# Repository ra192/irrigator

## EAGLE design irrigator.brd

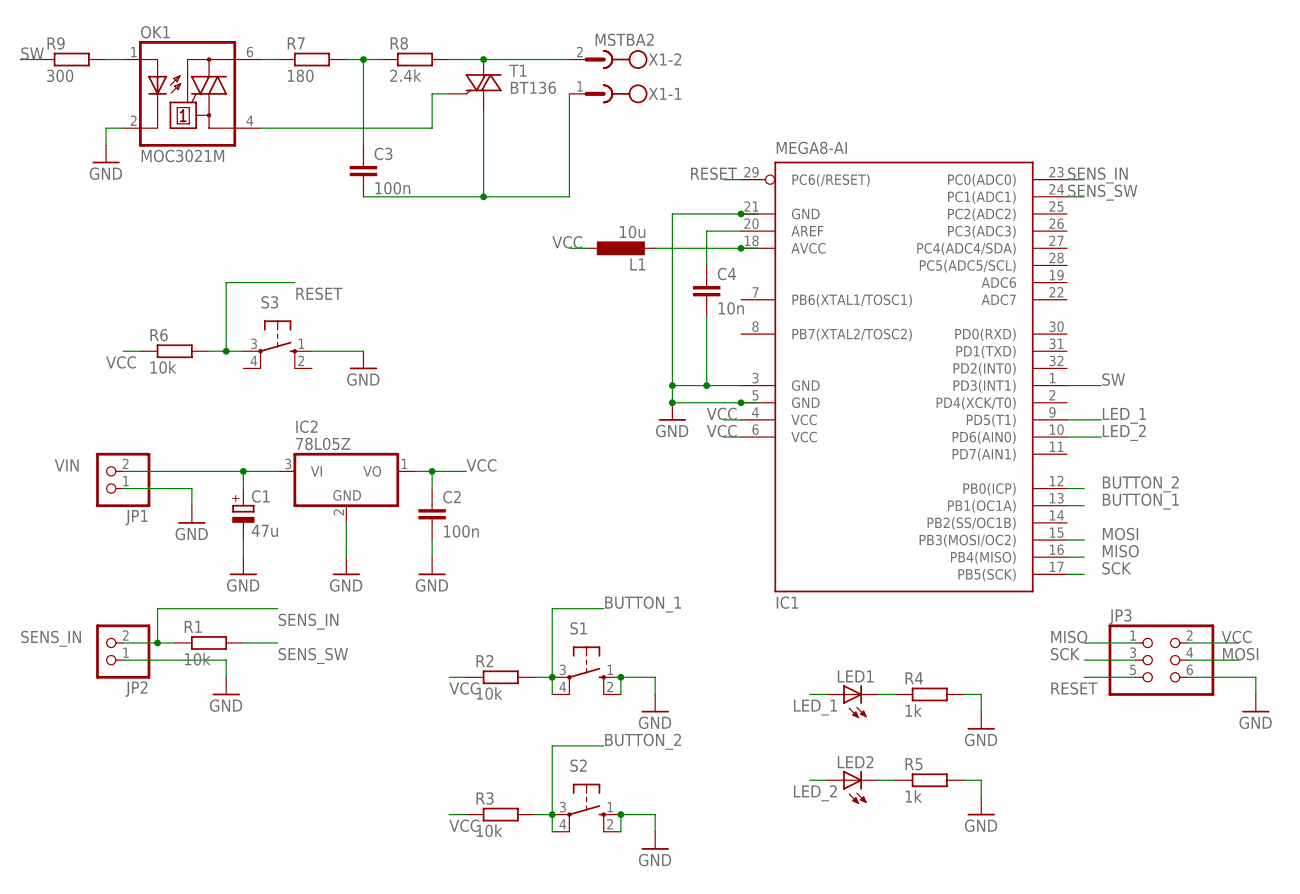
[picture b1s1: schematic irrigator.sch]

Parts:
C1: 47u; E2,5-6E
C2, C3: 100n; C1206
C4: 10n; C1206
IC1: MEGA8-AI; TQFP32-08
IC2: 78L05Z; TO92
JP1, JP2: PINHD-1X2; 1X02
JP3: PINHD-2X3; 2X03
L1: 10u; L3216C
LED1, LED2: LED5MM
OK1: MOC3021M; DIL06
R1, R2, R3, R6: 10k; R1206
R4, R5: 1k; R1206
R7: 180; R1206
R8: 2.4k; R1206
R9: 300; R1206
S1, S2, S3: 10-XX; B3F-10XX
T1: BT136; TO220AB
X1: MSTBA2

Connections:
BUTTON_1: IC1.13 (PB1(OC1A)), R2.2, S1.3, S1.4 (P1)
BUTTON_2: IC1.12 (PB0(ICP)), R3.2, S2.3, S2.4 (P1)
GND: C1.-, C2.2, C4.2, IC1.3 (GND), IC1.5 (GND), IC1.21 (GND), IC2.2 (GND), JP1.1, JP2.1, JP3.6, OK1.2 (C), R4.2, R5.2, S1.1 (S), S1.2 (S1), S2.1 (S), S2.2 (S1), S3.1 (S)
LED_1: IC1.9 (PD5(T1)), LED1.A
LED_2: IC1.10 (PD6(AIN0)), LED2.A
MISO: IC1.16 (PB4(MISO)), JP3.1
MOSI: IC1.15 (PB3(MOSI/OC2)), JP3.4
unnamed: OK1.1 (A), R9.2
unnamed: LED1.K (C), R4.1
unnamed: LED2.K (C), R5.1
unnamed: OK1.6 (A2), R7.1
unnamed: C3.1, R7.2, R8.1
unnamed: OK1.4 (A1), T1.3 (G)
unnamed: R8.2, T1.2 (A2), X1.2
unnamed: C3.2, T1.1 (A1), X1.1
unnamed: C4.1, IC1.20 (AREF)
unnamed: IC1.18 (AVCC), L1.2
RESET: IC1.29 (PC6(/RESET)), JP3.5, R6.2, S3.3
SCK: IC1.17 (PB5(SCK)), JP3.3
SENS_IN: IC1.23 (PC0(ADC0)), JP2.2, R1.1
SENS_SW: IC1.24 (PC1(ADC1)), R1.2
SW: IC1.1 (PD3(INT1)), R9.1
VCC: C2.1, IC1.4 (VCC), IC1.6 (VCC), IC2.1 (VO), JP3.2, L1.1, R2.1, R3.1, R6.1
VIN: C1.+, IC2.3 (VI), JP1.2

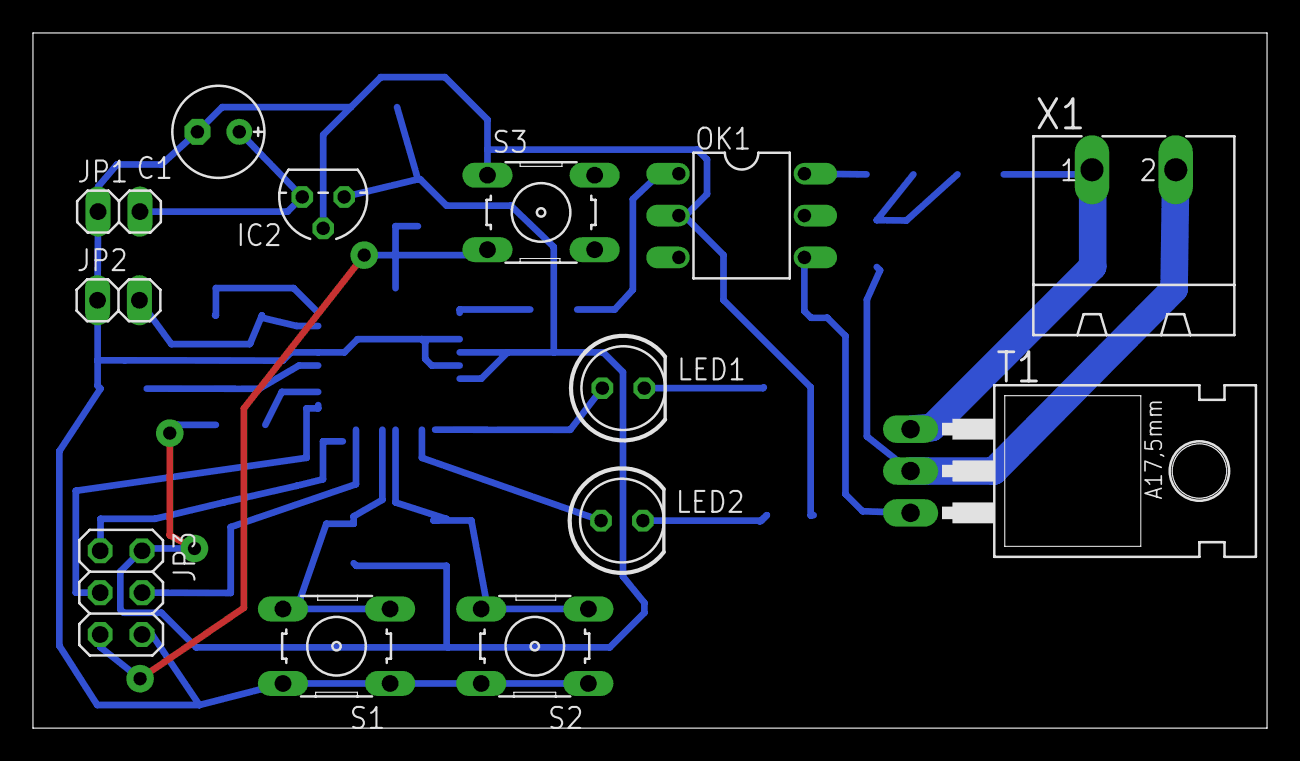
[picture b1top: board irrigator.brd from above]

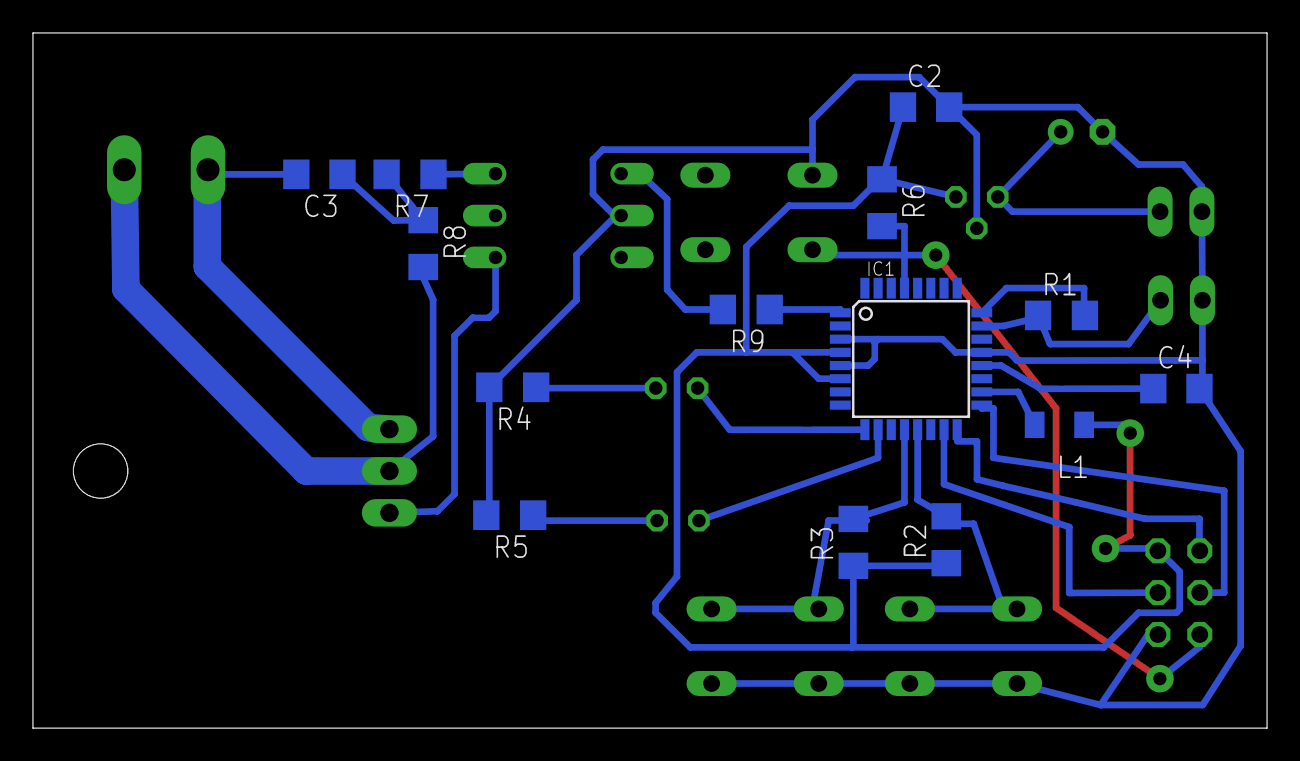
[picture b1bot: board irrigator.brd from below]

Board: 2 copper layers, 74.9 x 42.2 mm, 27 parts (14 on the bottom side), 24 nets.

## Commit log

2016-07-19 add swg
2016-07-19 svg changes
2016-12-18 reroute
2016-12-25 increase pwr net width
2016-12-25 board pdf
2016-12-27 fix. errors and manual routing
2016-12-27 minor fix.
2016-12-27 minor fix
2017-01-03 board fix
2017-01-03 brd fix.
2017-01-03 fix. and topor files
2017-01-03 pdf changes
2017-01-03 add svg
2017-01-03 fix.
2017-01-27 add sensor switch
